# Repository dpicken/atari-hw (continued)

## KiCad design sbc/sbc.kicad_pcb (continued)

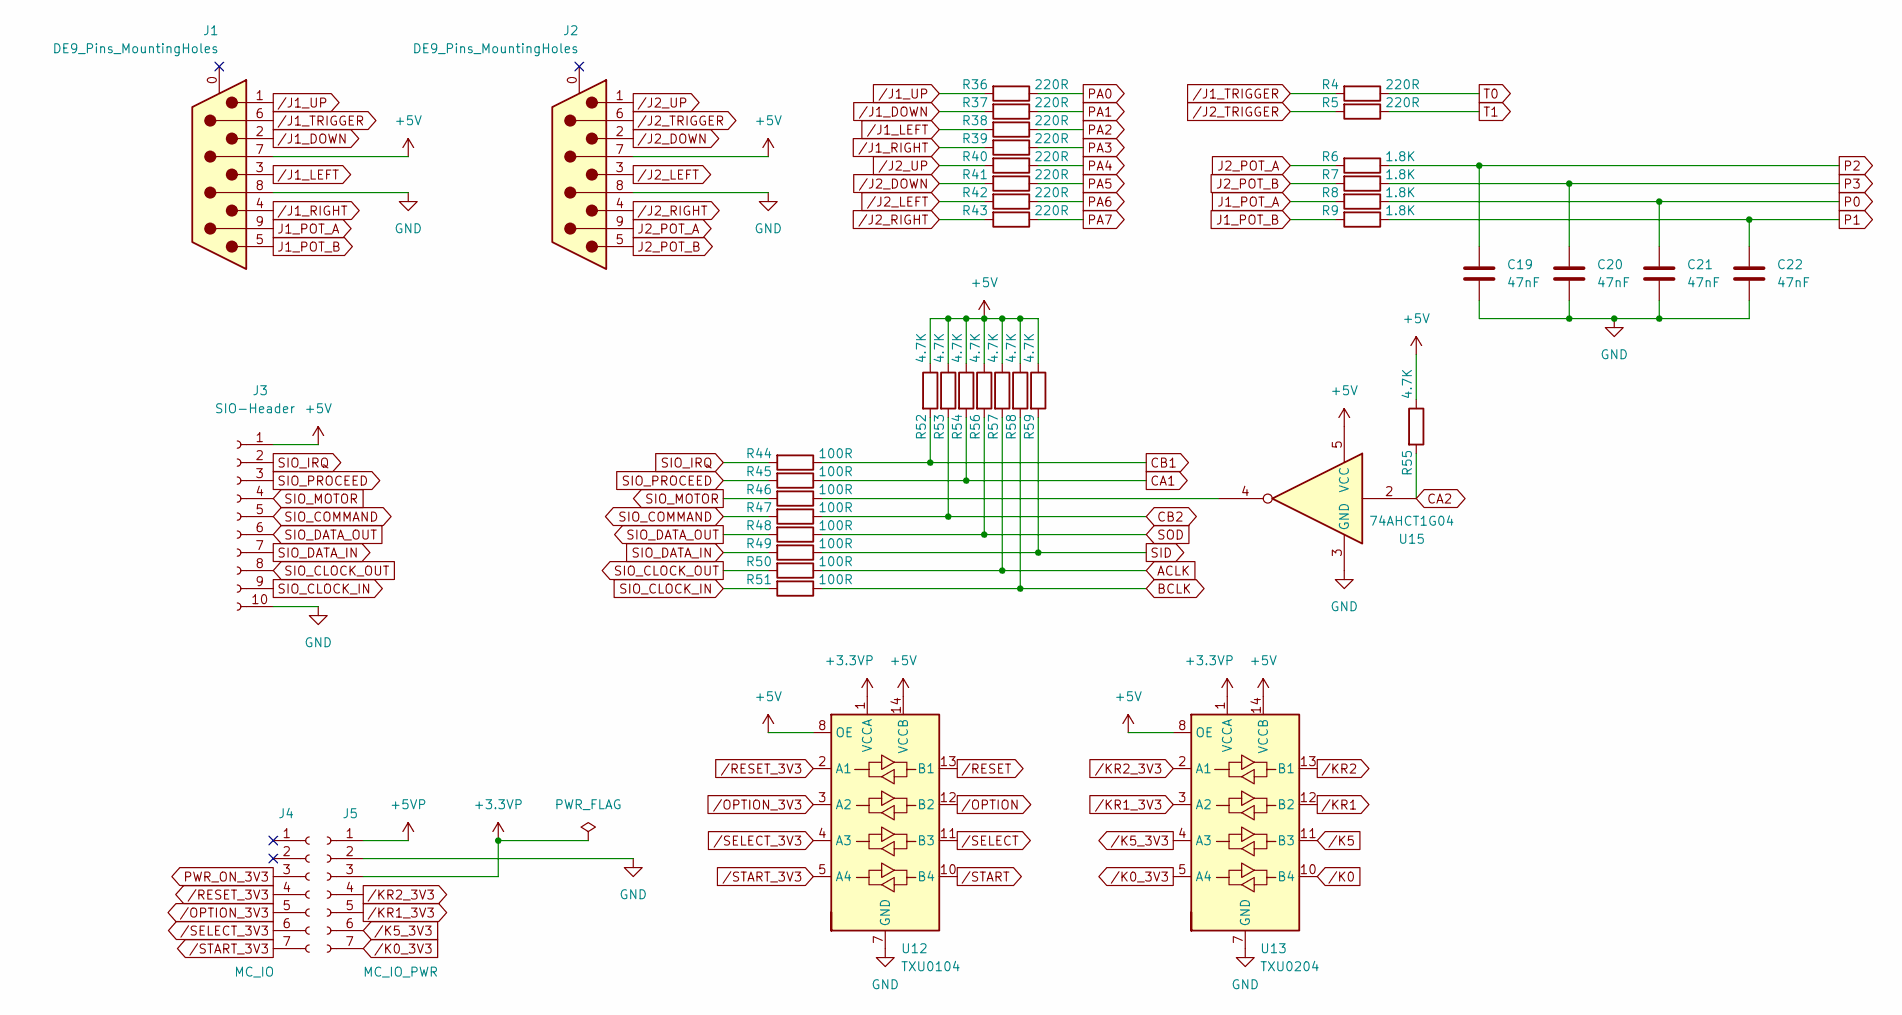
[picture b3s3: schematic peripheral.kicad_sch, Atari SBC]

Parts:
C19, C20, C21, C22: 47nF; C_0805_2012Metric_Pad1.18x1.45mm_HandSolder
J1, J2: DE9_Pins_MountingHoles; DSUB-9_Pins_Horizontal_P2.77x2.84mm_EdgePinOffset4.94mm_Hou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
J3: SIO-Header; PinSocket_1x10_P2.54mm_Vertical
J4: MC_IO; PinSocket_1x07_P2.54mm_Vertical
J5: MC_IO_PWR; PinSocket_1x07_P2.54mm_Vertical
R4, R5, R36, R37, R38, R39, R40, R41, R42, R43: 220R; R_0805_2012Metric_Pad1.20x1.40mm_HandSolder
R6, R7, R8, R9: 1.8K; R_0805_2012Metric_Pad1.20x1.40mm_HandSolder
R44, R45, R46, R47, R48, R49, R50, R51: 100R; R_0805_2012Metric_Pad1.20x1.40mm_HandSolder
R52, R53, R54, R55, R56, R57, R58, R59: 4.7K; R_0805_2012Metric_Pad1.20x1.40mm_HandSolder
U12: TXU0104; TSSOP-14_4.4x5mm_P0.65mm
U13: TXU0204; TSSOP-14_4.4x5mm_P0.65mm
U15: 74AHCT1G04; SOT-23-5_HandSoldering

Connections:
+3.3VP: J5.3, U12.1 (VCCA), U13.1 (VCCA); also elsewhere on the board
+5V: J1.7, J2.7, J3.1, R52.1, R53.1, R54.1, R55.1, R56.1, R57.1, R58.1, R59.1, U12.8 (OE), U12.14 (VCCB), U13.8 (OE), U13.14 (VCCB), U15.5 (VCC); also elsewhere on the board
+5VP: J5.1; also elsewhere on the board
ACLK: R50.1, R57.2; also elsewhere on the board
BCLK: R51.1, R58.2; also elsewhere on the board
CA1: R45.1, R54.2; also elsewhere on the board
CA2: R55.2, U15.2; also elsewhere on the board
CB1: R44.1, R52.2; also elsewhere on the board
CB2: R47.1, R53.2; also elsewhere on the board
GND: C19.2, C20.2, C21.2, C22.2, J1.8, J2.8, J3.10, J5.2, U12.7 (GND), U13.7 (GND), U15.3 (GND); also elsewhere on the board
J1_POT_A: J1.9, R8.2
J1_POT_B: J1.5, R9.2
J2_POT_A: J2.9, R6.2
J2_POT_B: J2.5, R7.2
unnamed: R46.1, U15.4
P0: C21.1, R8.1; also elsewhere on the board
P1: C22.1, R9.1; also elsewhere on the board
P2: C19.1, R6.1; also elsewhere on the board
P3: C20.1, R7.1; also elsewhere on the board
PA0: R36.1; also elsewhere on the board
PA1: R37.1; also elsewhere on the board
PA2: R38.1; also elsewhere on the board
PA3: R39.1; also elsewhere on the board
PA4: R40.1; also elsewhere on the board
PA5: R41.1; also elsewhere on the board
PA6: R42.1; also elsewhere on the board
PA7: R43.1; also elsewhere on the board
PWR_ON_3V3: J4.3; also elsewhere on the board
SID: R49.1, R59.2; also elsewhere on the board
SIO_CLOCK_IN: J3.9, R51.2
SIO_CLOCK_OUT: J3.8, R50.2
SIO_COMMAND: J3.5, R47.2
SIO_DATA_IN: J3.7, R49.2
SIO_DATA_OUT: J3.6, R48.2
SIO_IRQ: J3.2, R44.2
SIO_MOTOR: J3.4, R46.2
SIO_PROCEED: J3.3, R45.2
SOD: R48.1, R56.2; also elsewhere on the board
T0: R4.1; also elsewhere on the board
T1: R5.1; also elsewhere on the board
/J1_DOWN: J1.2, R37.2
/J1_LEFT: J1.3, R38.2
/J1_RIGHT: J1.4, R39.2
/J1_TRIGGER: J1.6, R4.2
/J1_UP: J1.1, R36.2
/J2_DOWN: J2.2, R41.2
/J2_LEFT: J2.3, R42.2
/J2_RIGHT: J2.4, R43.2
/J2_TRIGGER: J2.6, R5.2
/J2_UP: J2.1, R40.2
/K0: U13.10 (B4); also elsewhere on the board
/K0_3V3: J5.7, U13.5 (A4)
/K5: U13.11 (B3); also elsewhere on the board
/K5_3V3: J5.6, U13.4 (A3)
/KR1: U13.12 (B2); also elsewhere on the board
/KR1_3V3: J5.5, U13.3 (A2)
/KR2: U13.13 (B1); also elsewhere on the board
/KR2_3V3: J5.4, U13.2 (A1)
/OPTION: U12.12 (B2); also elsewhere on the board
/OPTION_3V3: J4.5, U12.3 (A2)
/RESET: U12.13 (B1); also elsewhere on the board
/RESET_3V3: J4.4, U12.2 (A1)
/SELECT: U12.11 (B3); also elsewhere on the board
/SELECT_3V3: J4.6, U12.4 (A3)
/START: U12.10 (B4); also elsewhere on the board
/START_3V3: J4.7, U12.5 (A4)

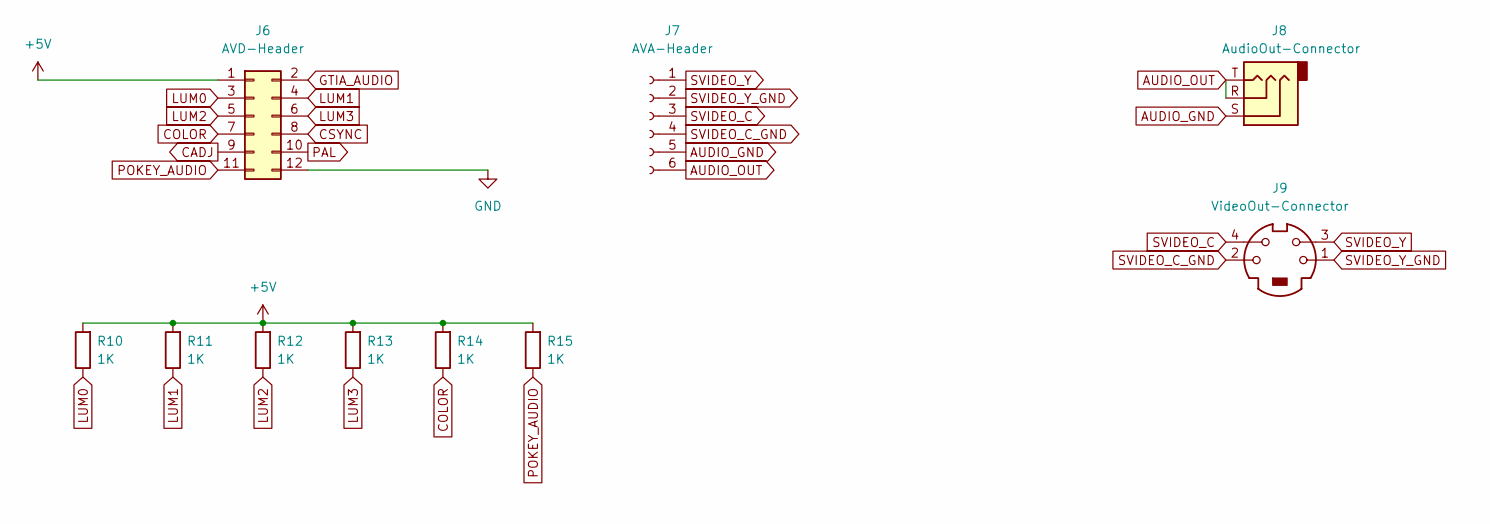
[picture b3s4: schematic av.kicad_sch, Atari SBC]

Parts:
J6: AVD-Header; PinSocket_2x06_P2.54mm_Vertical
J7: AVA-Header; PinSocket_1x06_P2.54mm_Vertical
J8: AudioOut-Connector; Jack_3.5mm_CUI_SJ1-3533NG_Horizontal
J9: VideoOut-Connector; 57492631
R10, R11, R12, R13, R14, R15: 1K; R_0805_2012Metric_Pad1.20x1.40mm_HandSolder

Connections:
+5V: J6.1, R10.2, R11.2, R12.2, R13.2, R14.2, R15.2; also elsewhere on the board
AUDIO_GND: J7.5, J8.S
AUDIO_OUT: J7.6, J8.R, J8.T
CADJ: J6.9; also elsewhere on the board
COLOR: J6.7, R14.1; also elsewhere on the board
CSYNC: J6.8; also elsewhere on the board
GND: J6.12; also elsewhere on the board
GTIA_AUDIO: J6.2; also elsewhere on the board
LUM0: J6.3, R10.1; also elsewhere on the board
LUM1: J6.4, R11.1; also elsewhere on the board
LUM2: J6.5, R12.1; also elsewhere on the board
LUM3: J6.6, R13.1; also elsewhere on the board
PAL: J6.10; also elsewhere on the board
POKEY_AUDIO: J6.11, R15.1; also elsewhere on the board
SVIDEO_C: J7.3, J9.4
SVIDEO_C_GND: J7.4, J9.2
SVIDEO_Y: J7.1, J9.3
SVIDEO_Y_GND: J7.2, J9.1

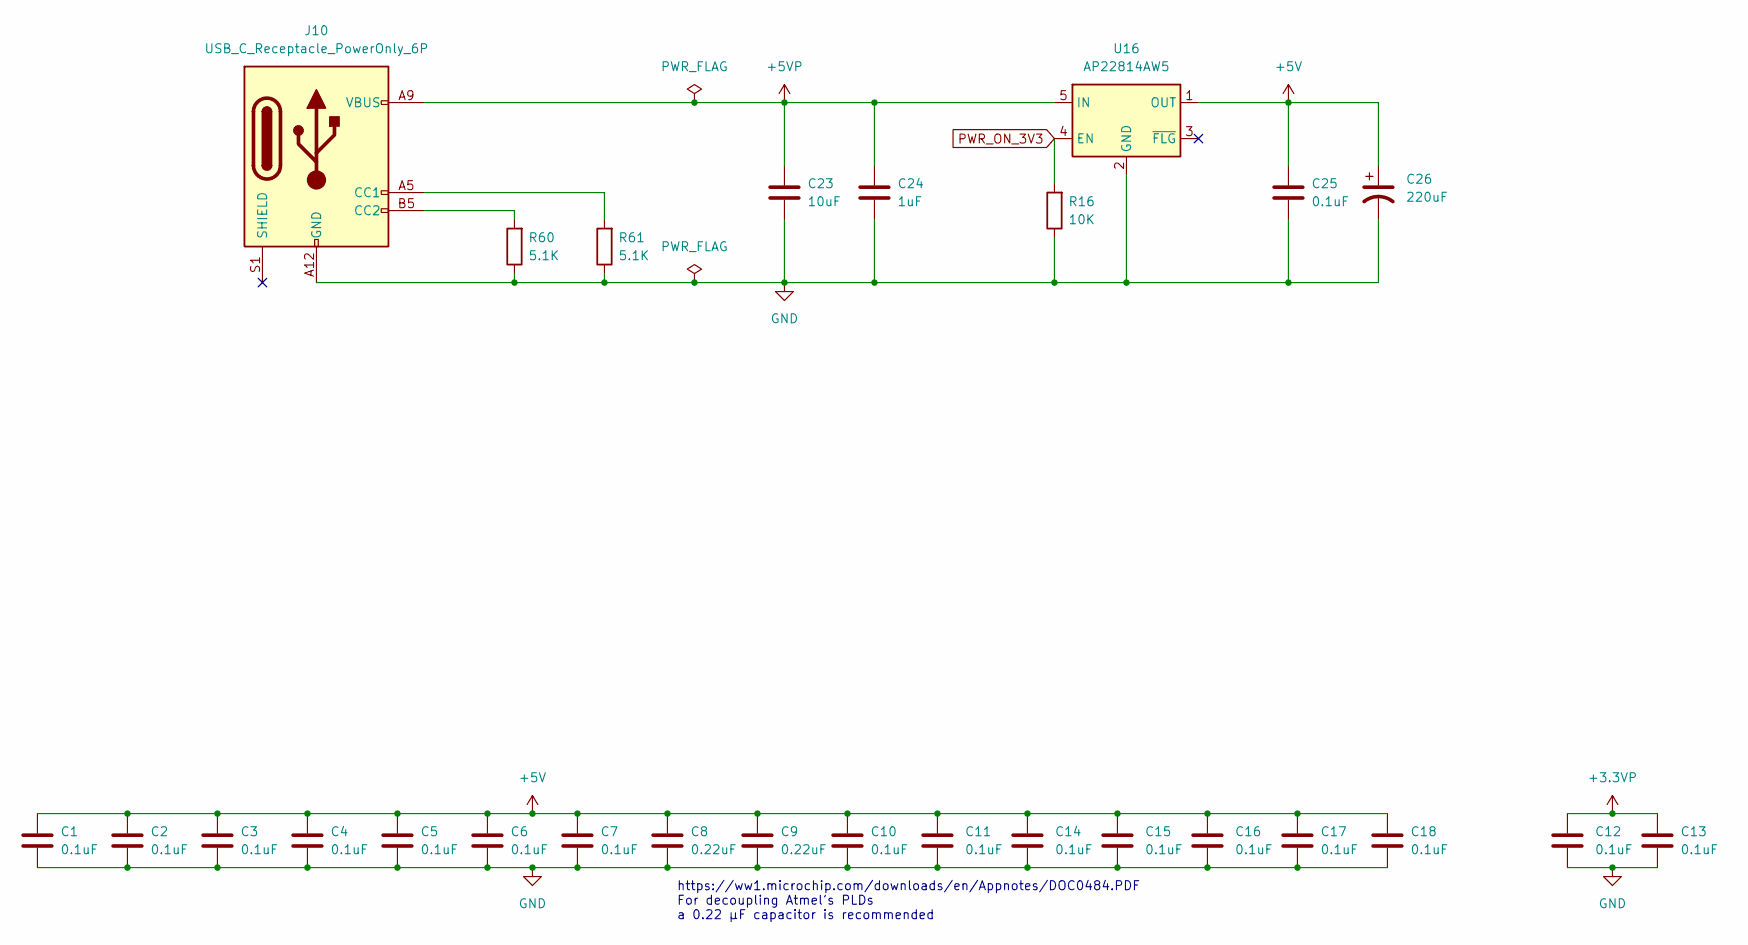
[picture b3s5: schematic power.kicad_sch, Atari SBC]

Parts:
C1, C2, C3, C4, C5, C6, C7, C10, C11, C12, C13, C14, C15, C16, C17, C18, C25: 0.1uF; C_0805_2012Metric_Pad1.18x1.45mm_HandSolder
C8, C9: 0.22uF; C_0805_2012Metric_Pad1.18x1.45mm_HandSolder
C23: 10uF; C_0805_2012Metric_Pad1.18x1.45mm_HandSolder
C24: 1uF; C_0805_2012Metric_Pad1.18x1.45mm_HandSolder
C26: 220uF; CP_Radial_D6.3mm_P2.50mm
J10: USB_C_Receptacle_PowerOnly_6P; USB_C_Receptacle_GCT_USB4125-xx-x_6P_TopMnt_Horizontal
R16: 10K; R_0805_2012Metric_Pad1.20x1.40mm_HandSolder
R60, R61: 5.1K; R_0805_2012Metric_Pad1.20x1.40mm_HandSolder
U16: AP22814AW5; SOT-23-5

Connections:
+3.3VP: C12.1, C13.1; also elsewhere on the board
+5V: C1.1, C2.1, C3.1, C4.1, C5.1, C6.1, C7.1, C8.1, C9.1, C10.1, C11.1, C14.1, C15.1, C16.1, C17.1, C18.1, C25.1, C26.1, U16.1 (OUT); also elsewhere on the board
+5VP: C23.1, C24.1, J10.A9 (VBUS), J10.B9 (VBUS), U16.5 (IN); also elsewhere on the board
GND: C1.2, C2.2, C3.2, C4.2, C5.2, C6.2, C7.2, C8.2, C9.2, C10.2, C11.2, C12.2, C13.2, C14.2, C15.2, C16.2, C17.2, C18.2, C23.2, C24.2, C25.2, C26.2, J10.A12 (GND), J10.B12 (GND), R16.1, R60.1, R61.1, U16.2 (GND); also elsewhere on the board
unnamed: J10.A5 (CC1), R61.2
unnamed: J10.B5 (CC2), R60.2
PWR_ON_3V3: R16.2, U16.4 (EN); also elsewhere on the board

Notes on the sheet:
https://ww1.microchip.com/downloads/en/Appnotes/DOC0484.PDF For decoupling Atmel's PLDs a 0.22 μF capacitor is recommended

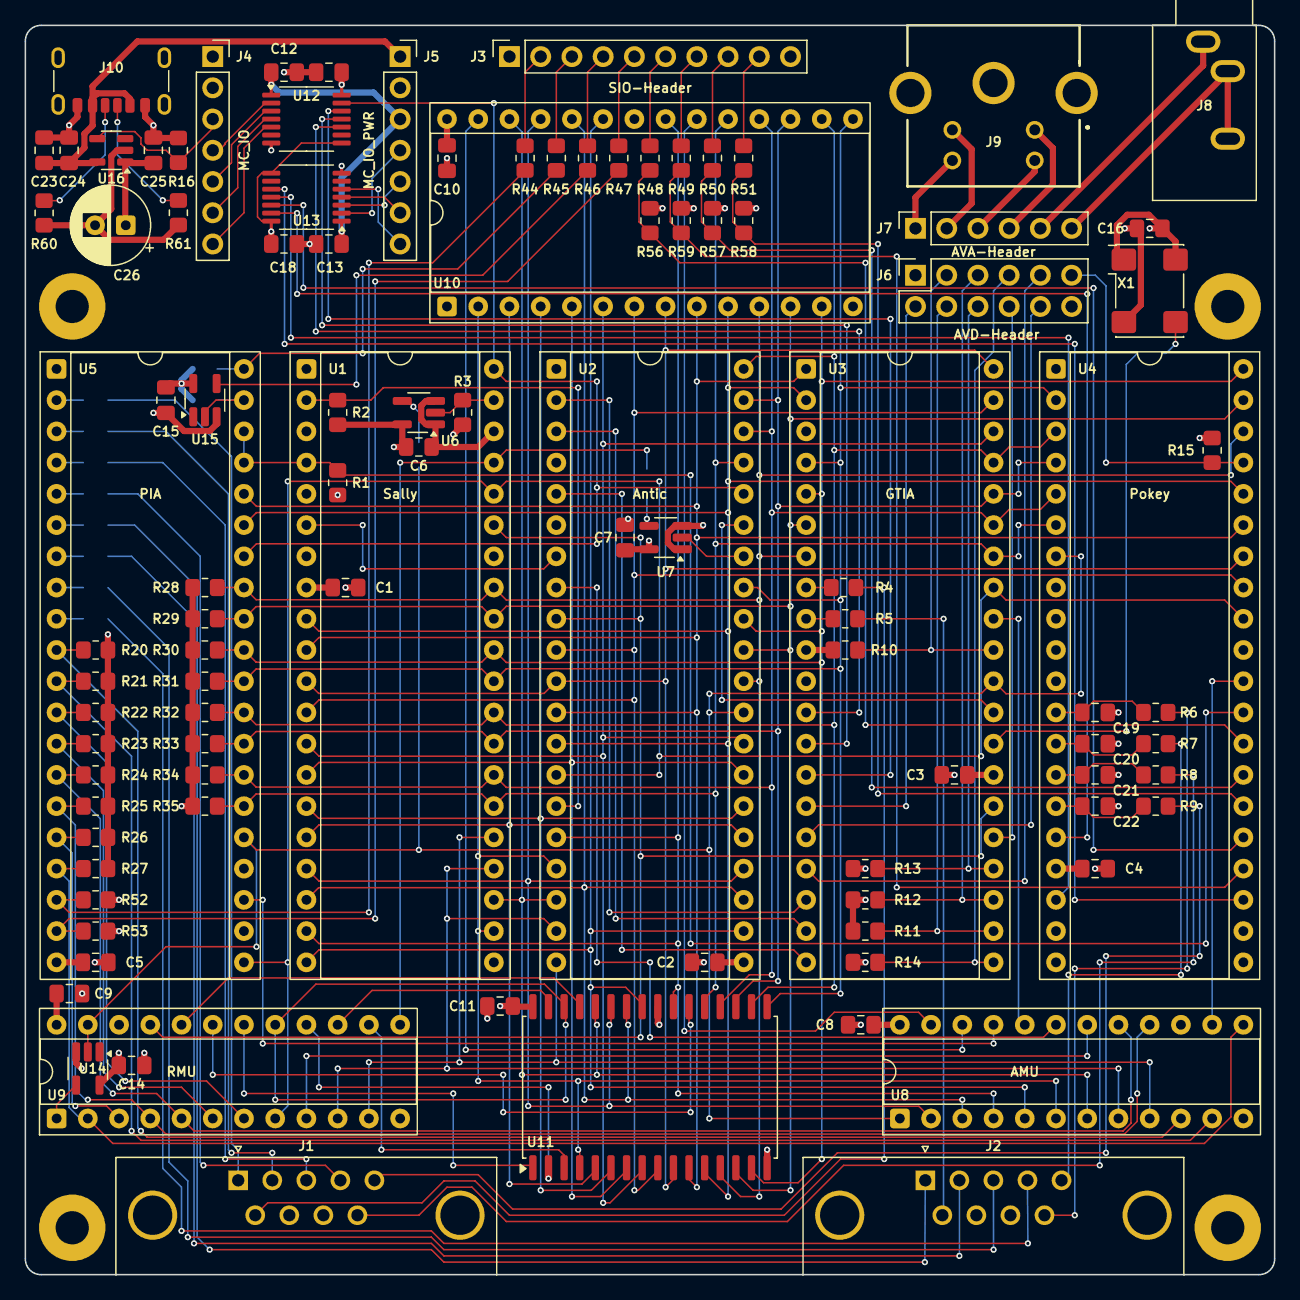
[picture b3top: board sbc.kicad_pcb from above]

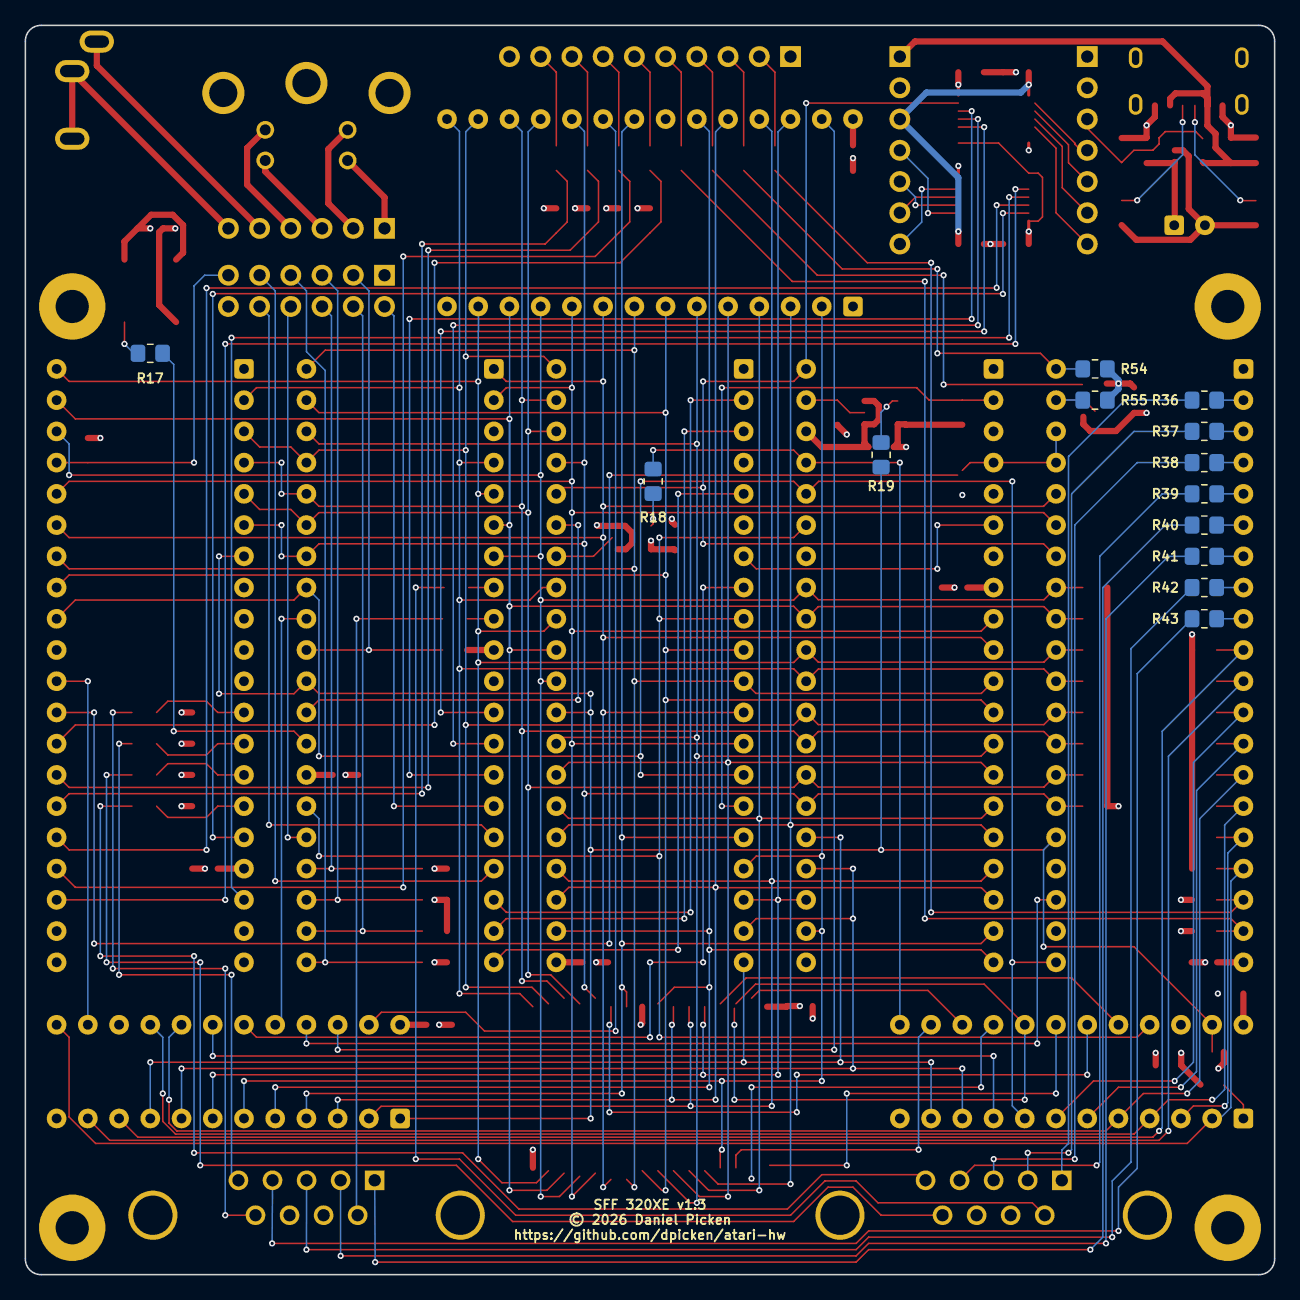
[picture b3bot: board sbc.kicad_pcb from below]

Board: 4 copper layers, 101.6 x 101.6 mm, 118 parts (13 on the bottom side), 148 nets.

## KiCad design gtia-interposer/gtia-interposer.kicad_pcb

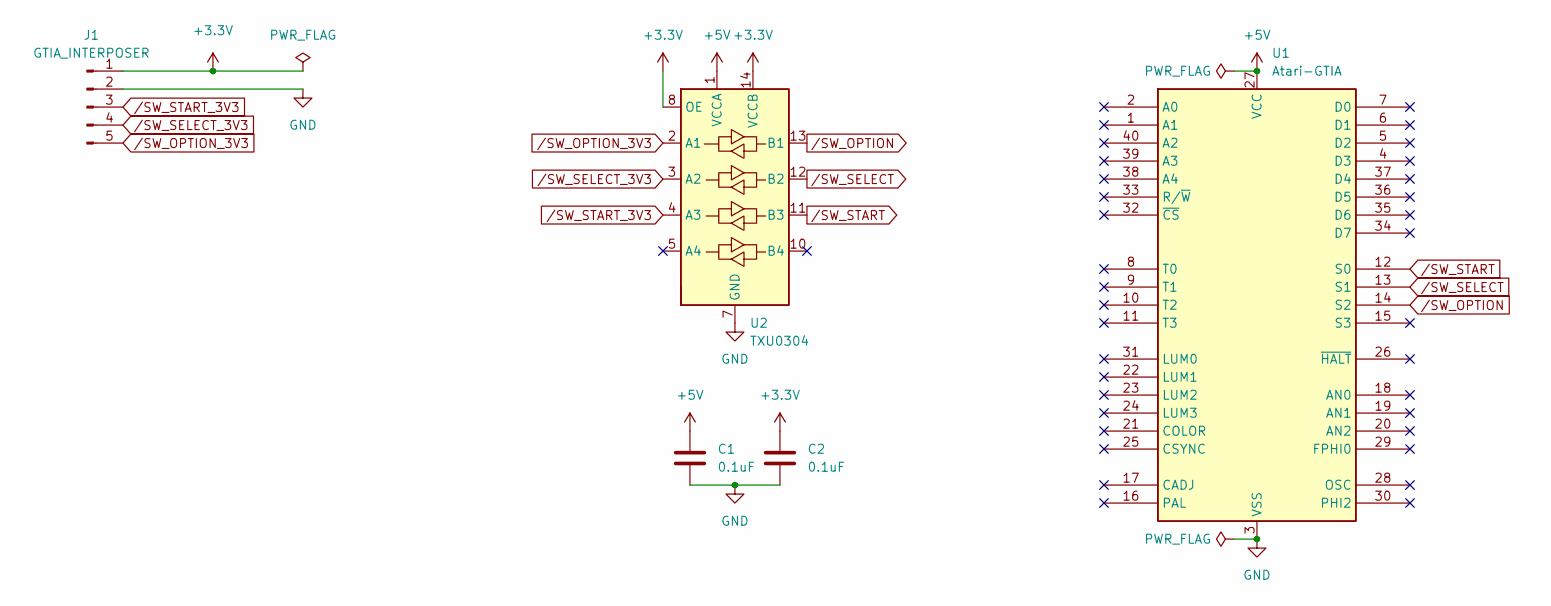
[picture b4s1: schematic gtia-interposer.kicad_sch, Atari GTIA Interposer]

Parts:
C1, C2: 0.1uF; C_0805_2012Metric_Pad1.18x1.45mm_HandSolder
J1: GTIA_INTERPOSER; PinHeader_1x05_P2.54mm_Vertical
U1: Atari-GTIA; DIP-40_W15.24mm_Socket
U2: TXU0304; TSSOP-14_4.4x5mm_P0.65mm

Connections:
+3V3: C2.1, J1.1, U2.8 (OE), U2.14 (VCCB)
+5V: C1.1, U1.27 (VCC), U2.1 (VCCA)
GND: C1.2, C2.2, J1.2, U1.3 (VSS), U2.7 (GND)
/SW_OPTION: U1.14 (S2), U2.13 (B1)
/SW_OPTION_3V3: J1.5, U2.2 (A1)
/SW_SELECT: U1.13 (S1), U2.12 (B2)
/SW_SELECT_3V3: J1.4, U2.3 (A2)
/SW_START: U1.12 (S0), U2.11 (B3)
/SW_START_3V3: J1.3, U2.4 (A3)

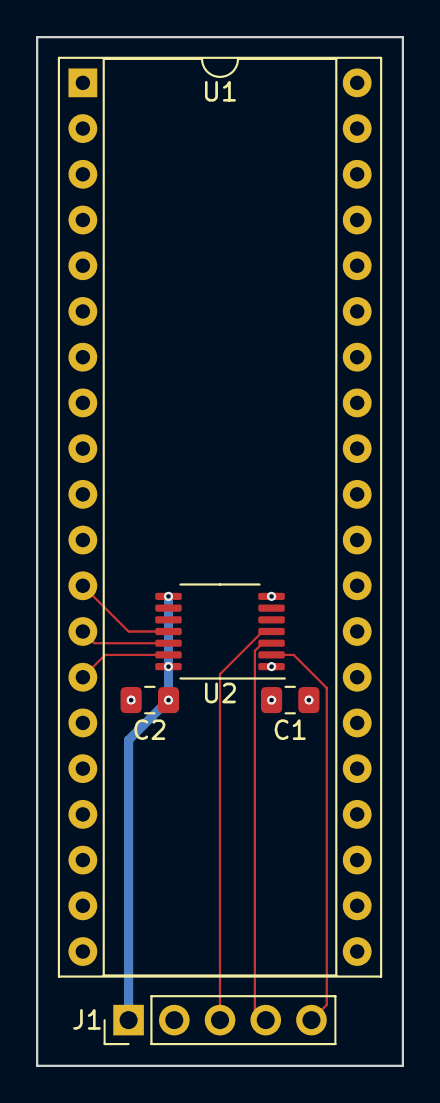
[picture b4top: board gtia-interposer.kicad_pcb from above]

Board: 4 copper layers, 20.3 x 57.2 mm, 5 parts (0 on the bottom side), 9 nets.

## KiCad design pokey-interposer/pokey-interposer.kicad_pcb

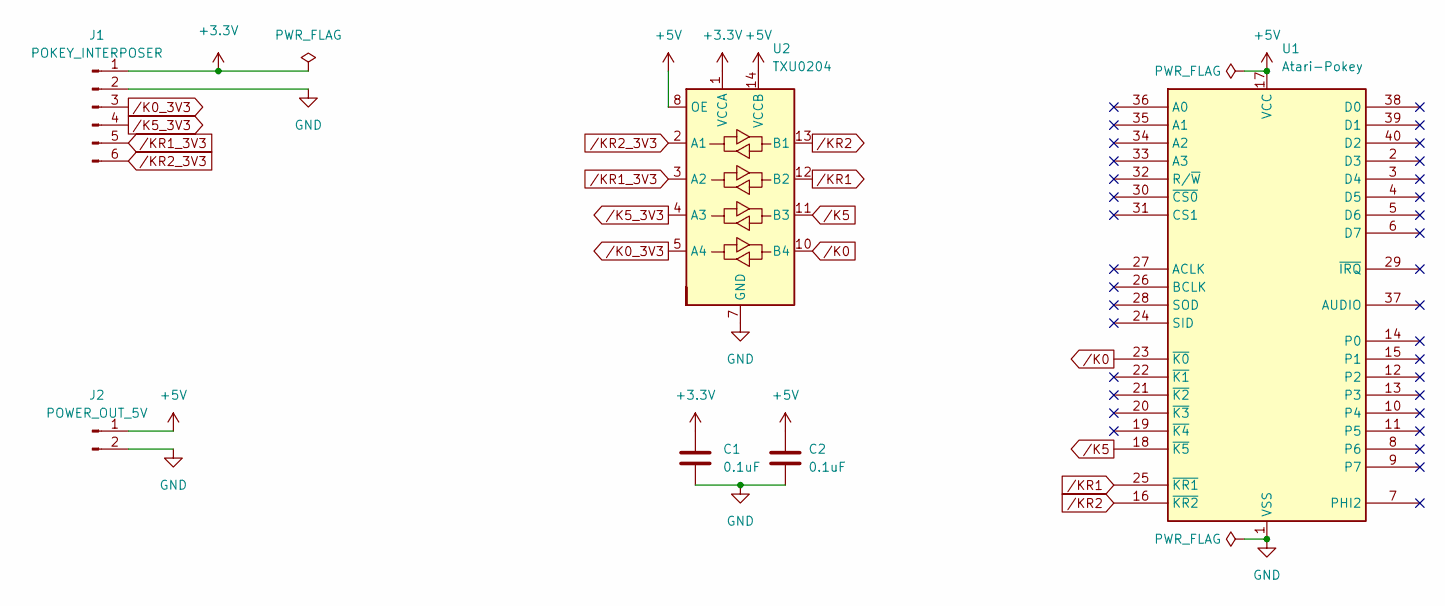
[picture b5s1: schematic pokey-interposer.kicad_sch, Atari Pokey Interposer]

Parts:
C1, C2: 0.1uF; C_0805_2012Metric_Pad1.18x1.45mm_HandSolder
J1: POKEY_INTERPOSER; PinHeader_1x06_P2.54mm_Vertical
J2: POWER_OUT_5V; PinHeader_1x02_P2.54mm_Vertical
U1: Atari-Pokey; DIP-40_W15.24mm_Socket
U2: TXU0204; TSSOP-14_4.4x5mm_P0.65mm

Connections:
+3V3: C1.1, J1.1, U2.1 (VCCA)
+5V: C2.1, J2.1, U1.17 (VCC), U2.8 (OE), U2.14 (VCCB)
GND: C1.2, C2.2, J1.2, J2.2, U1.1 (VSS), U2.7 (GND)
/K0: U1.23 (~K0), U2.10 (B4)
/K0_3V3: J1.3, U2.5 (A4)
/K5: U1.18 (~K5), U2.11 (B3)
/K5_3V3: J1.4, U2.4 (A3)
/KR1: U1.25 (~KR1), U2.12 (B2)
/KR1_3V3: J1.5, U2.3 (A2)
/KR2: U1.16 (~KR2), U2.13 (B1)
/KR2_3V3: J1.6, U2.2 (A1)

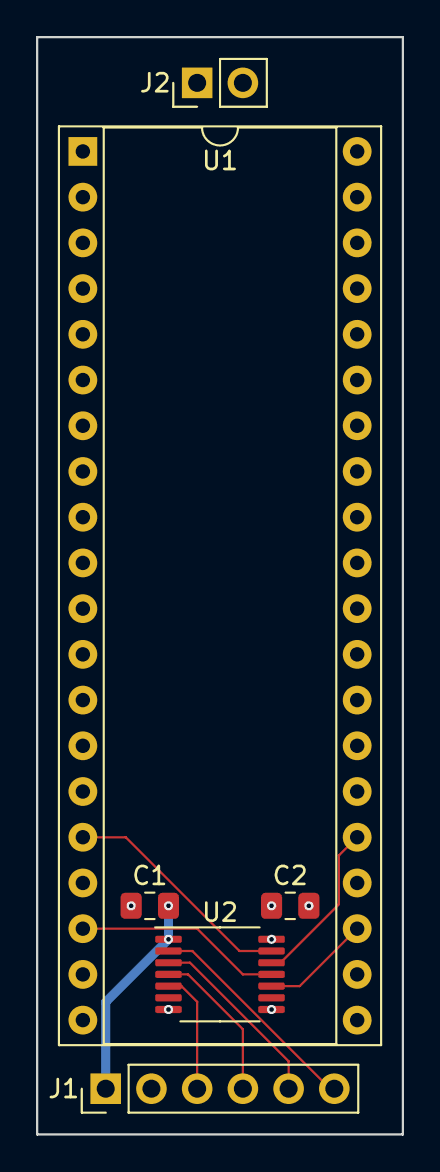
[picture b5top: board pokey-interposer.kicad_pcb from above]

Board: 4 copper layers, 20.3 x 61.0 mm, 6 parts (0 on the bottom side), 11 nets.

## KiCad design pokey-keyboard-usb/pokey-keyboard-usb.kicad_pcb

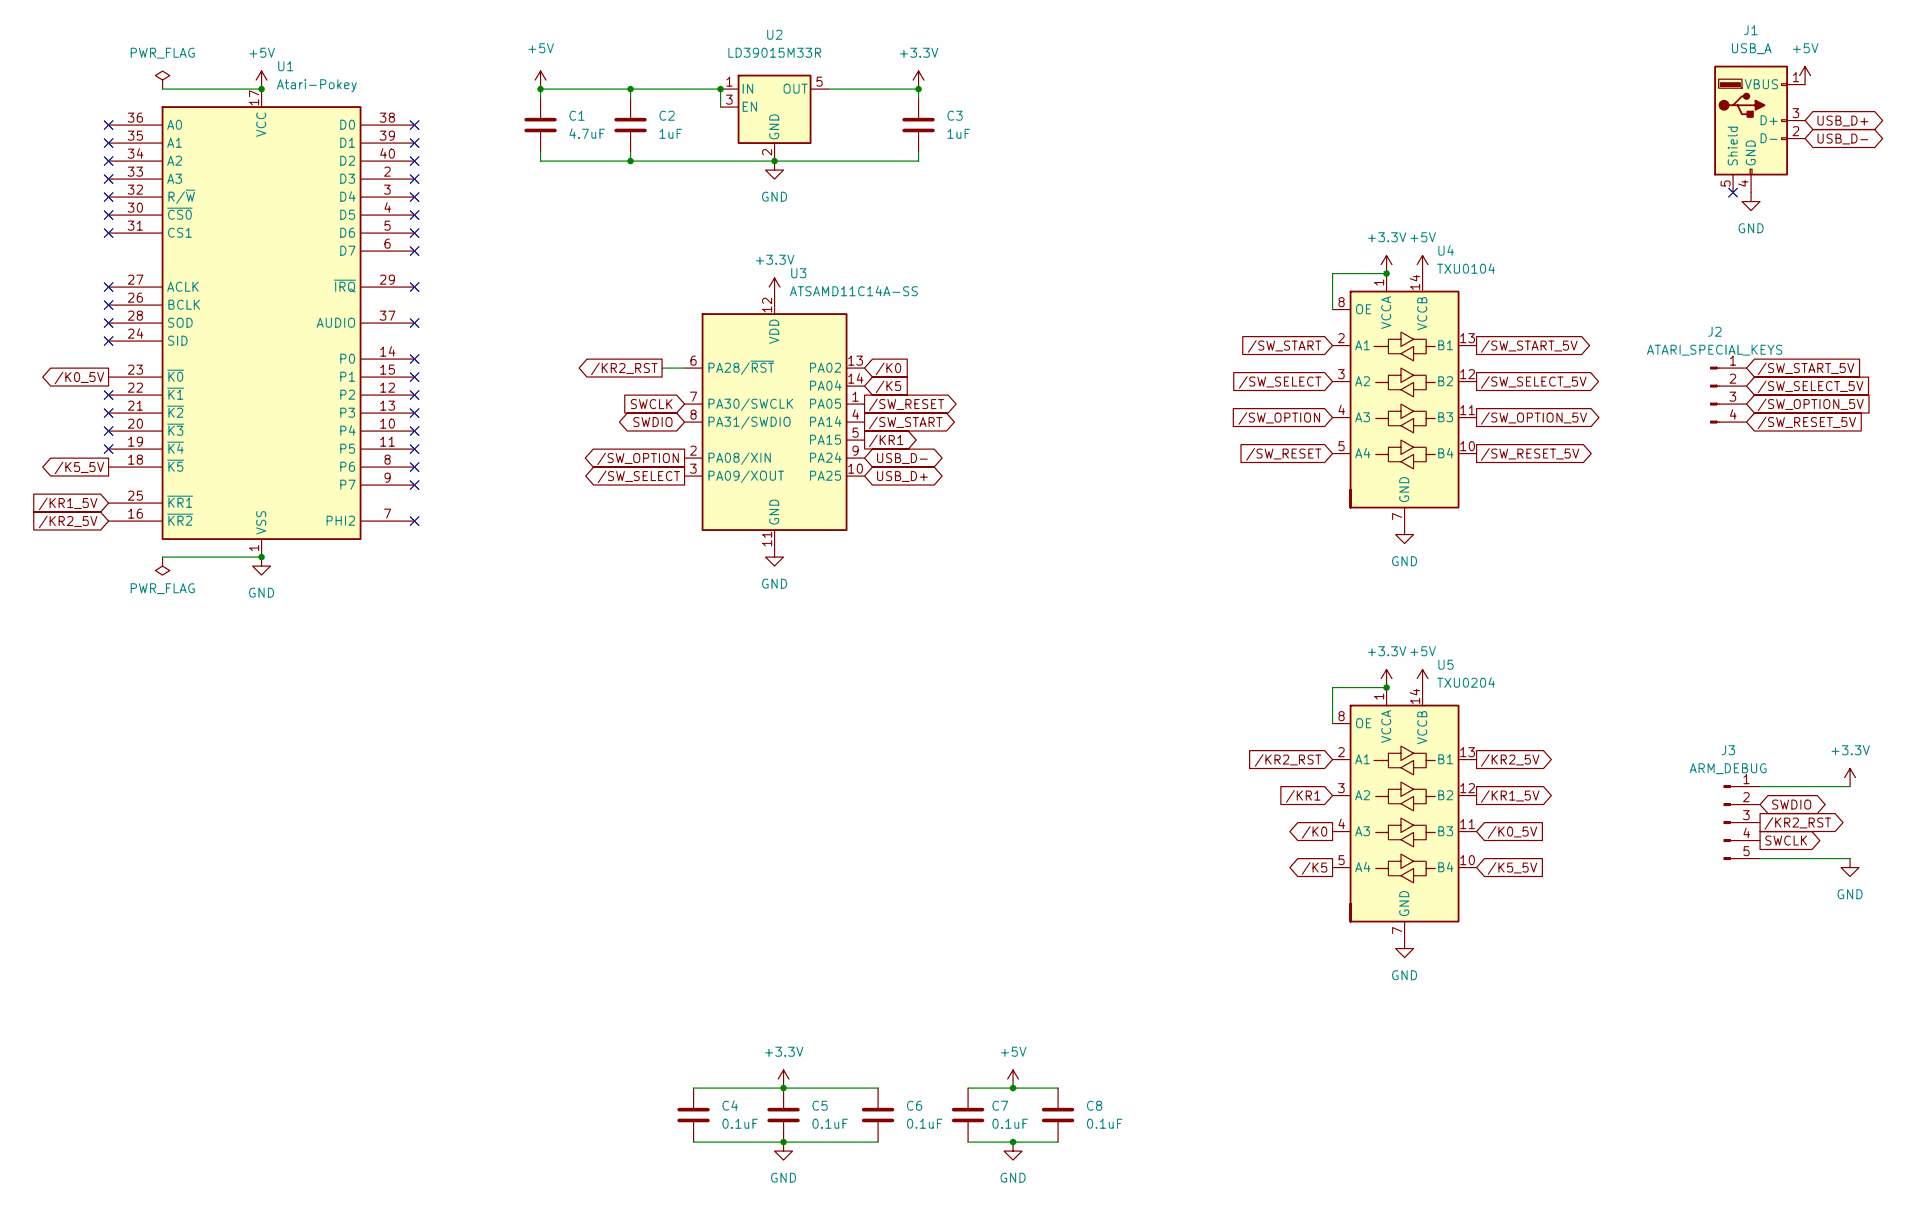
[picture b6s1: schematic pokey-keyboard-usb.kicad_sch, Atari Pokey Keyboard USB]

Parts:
C1: 4.7uF; C_0805_2012Metric_Pad1.18x1.45mm_HandSolder
C2, C3: 1uF; C_0805_2012Metric_Pad1.18x1.45mm_HandSolder
C4, C5, C6, C7, C8: 0.1uF; C_0805_2012Metric_Pad1.18x1.45mm_HandSolder
J1: USB_A; USB_A_Molex_67643_Horizontal
J2: ATARI_SPECIAL_KEYS; PinHeader_1x04_P2.54mm_Vertical
J3: ARM_DEBUG; PinHeader_1x05_P2.54mm_Vertical
U1: Atari-Pokey; DIP-40_W15.24mm_Socket
U2: LD39015M33R; SOT-23-5_HandSoldering
U3: ATSAMD11C14A-SS; SOIC-14_3.9x8.7mm_P1.27mm
U4: TXU0104; SOIC-14_3.9x8.7mm_P1.27mm
U5: TXU0204; SOIC-14_3.9x8.7mm_P1.27mm

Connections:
+3V3: C3.1, C4.1, C5.1, C6.1, J3.1, U2.5 (OUT), U3.12 (VDD), U4.1 (VCCA), U4.8 (OE), U5.1 (VCCA), U5.8 (OE)
+5V: C1.1, C2.1, C7.1, C8.1, J1.1 (VBUS), U1.17 (VCC), U2.1 (IN), U2.3 (EN), U4.14 (VCCB), U5.14 (VCCB)
GND: C1.2, C2.2, C3.2, C4.2, C5.2, C6.2, C7.2, C8.2, J1.4 (GND), J3.5, U1.1 (VSS), U2.2 (GND), U3.11 (GND), U4.7 (GND), U5.7 (GND)
SWCLK: J3.4, U3.7 (PA30/SWCLK)
SWDIO: J3.2, U3.8 (PA31/SWDIO)
USB_D+: J1.3 (D+), U3.10 (PA25)
USB_D-: J1.2 (D-), U3.9 (PA24)
/K0: U3.13 (PA02), U5.4 (A3)
/K0_5V: U1.23 (~K0), U5.11 (B3)
/K5: U3.14 (PA04), U5.5 (A4)
/K5_5V: U1.18 (~K5), U5.10 (B4)
/KR1: U3.5 (PA15), U5.3 (A2)
/KR1_5V: U1.25 (~KR1), U5.12 (B2)
/KR2_5V: U1.16 (~KR2), U5.13 (B1)
/KR2_RST: J3.3, U3.6 (PA28/~RST), U5.2 (A1)
/SW_OPTION: U3.2 (PA08/XIN), U4.4 (A3)
/SW_OPTION_5V: J2.3, U4.11 (B3)
/SW_RESET: U3.1 (PA05), U4.5 (A4)
/SW_RESET_5V: J2.4, U4.10 (B4)
/SW_SELECT: U3.3 (PA09/XOUT), U4.3 (A2)
/SW_SELECT_5V: J2.2, U4.12 (B2)
/SW_START: U3.4 (PA14), U4.2 (A1)
/SW_START_5V: J2.1, U4.13 (B1)

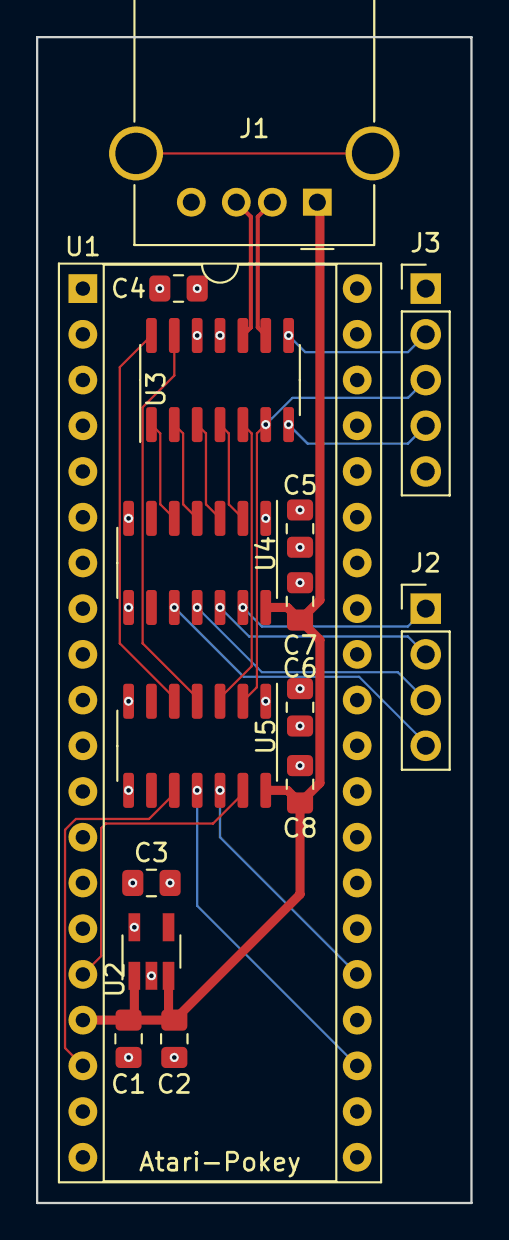
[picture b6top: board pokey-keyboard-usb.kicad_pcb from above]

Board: 4 copper layers, 24.1 x 64.8 mm, 16 parts (0 on the bottom side), 23 nets.

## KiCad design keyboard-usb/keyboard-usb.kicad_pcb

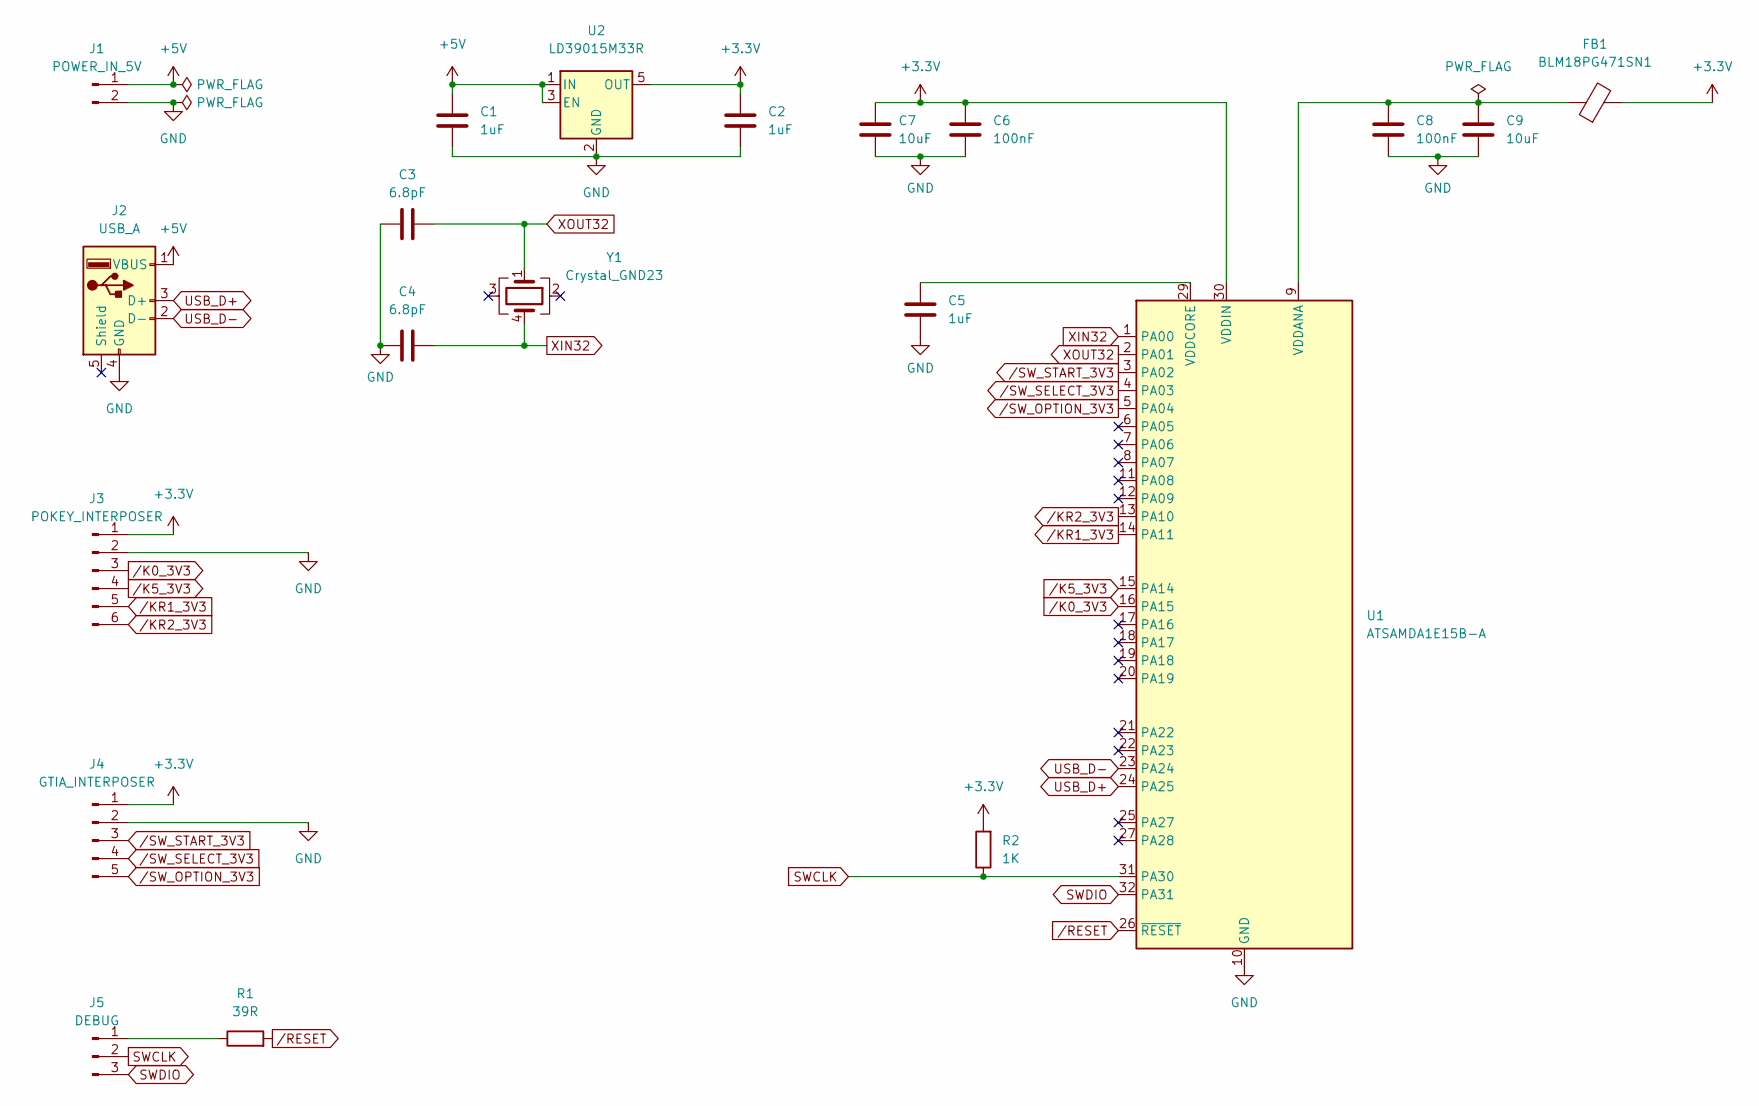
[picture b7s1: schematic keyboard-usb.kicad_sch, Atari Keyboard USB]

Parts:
C1, C2, C5: 1uF; C_0805_2012Metric_Pad1.18x1.45mm_HandSolder
C3, C4: 6.8pF; C_0805_2012Metric_Pad1.18x1.45mm_HandSolder
C6, C8: 100nF; C_0805_2012Metric_Pad1.18x1.45mm_HandSolder
C7, C9: 10uF; C_0805_2012Metric_Pad1.18x1.45mm_HandSolder
FB1: BLM18PG471SN1; R_0805_2012Metric_Pad1.20x1.40mm_HandSolder
J1: POWER_IN_5V; PinHeader_1x02_P2.54mm_Vertical
J2: USB_A; USB_A_Molex_67643_Horizontal
J3: POKEY_INTERPOSER; PinHeader_1x06_P2.54mm_Vertical
J4: GTIA_INTERPOSER; PinHeader_1x05_P2.54mm_Vertical
J5: DEBUG; PinHeader_1x03_P2.54mm_Vertical
R1: 39R; R_0805_2012Metric_Pad1.20x1.40mm_HandSolder
R2: 1K; R_0805_2012Metric_Pad1.20x1.40mm_HandSolder
U1: ATSAMDA1E15B-A; TQFP-32_7x7mm_P0.8mm
U2: LD39015M33R; SOT-23-5_HandSoldering
Y1: Crystal_GND23; Crystal_SMD_SeikoEpson_MC146-4Pin_6.7x1.5mm_HandSoldering

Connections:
+3V3: C2.1, C6.1, C7.1, FB1.2, J3.1, J4.1, R2.2, U1.30 (VDDIN), U2.5 (OUT)
+5V: C1.1, J1.1, J2.1 (VBUS), U2.1 (IN), U2.3 (EN)
GND: C1.2, C2.2, C3.2, C4.1, C5.2, C6.2, C7.2, C8.2, C9.2, J1.2, J2.4 (GND), J3.2, J4.2, U1.10 (GND), U1.28 (GND), U2.2 (GND)
unnamed: C5.1, U1.29 (VDDCORE)
unnamed: C8.1, C9.1, FB1.1, U1.9 (VDDANA)
unnamed: J5.1, R1.1
SWCLK: J5.2, R2.1, U1.31 (PA30)
SWDIO: J5.3, U1.32 (PA31)
USB_D+: J2.3 (D+), U1.24 (PA25)
USB_D-: J2.2 (D-), U1.23 (PA24)
XIN32: C4.2, U1.1 (PA00), Y1.4
XOUT32: C3.1, U1.2 (PA01), Y1.1
/K0_3V3: J3.3, U1.16 (PA15)
/K5_3V3: J3.4, U1.15 (PA14)
/KR1_3V3: J3.5, U1.14 (PA11)
/KR2_3V3: J3.6, U1.13 (PA10)
/RESET: R1.2, U1.26 (~RESET)
/SW_OPTION_3V3: J4.5, U1.5 (PA04)
/SW_SELECT_3V3: J4.4, U1.4 (PA03)
/SW_START_3V3: J4.3, U1.3 (PA02)

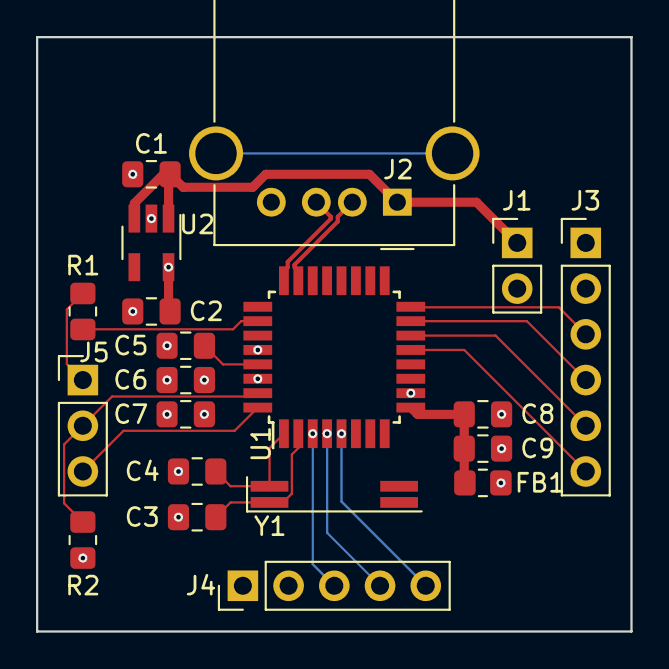
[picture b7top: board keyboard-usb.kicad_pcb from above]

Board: 4 copper layers, 33.0 x 33.0 mm, 20 parts (0 on the bottom side), 20 nets.
